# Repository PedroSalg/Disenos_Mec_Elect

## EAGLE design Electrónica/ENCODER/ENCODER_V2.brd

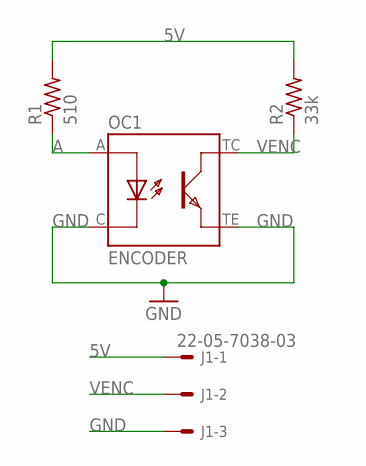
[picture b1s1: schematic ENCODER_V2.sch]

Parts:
J1: 22-05-7038-03; 7395-03
OC1: ENCODER; PI_GP1S53VJ000F
R1: 510; R0805
R2: 33k; R0805

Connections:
5V: J1.1, R1.2, R2.2
A: OC1.A, R1.1
GND: J1.3, OC1.C, OC1.TE
VENC: J1.2, OC1.TC, R2.1

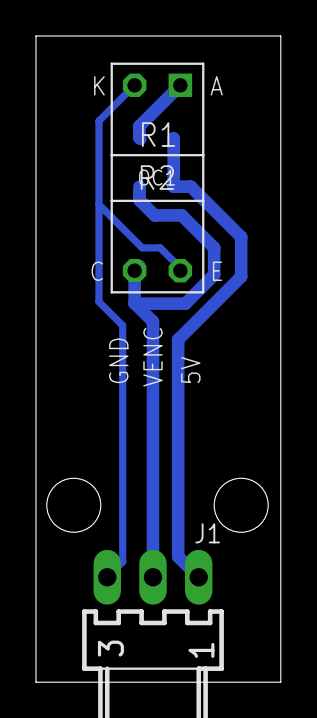
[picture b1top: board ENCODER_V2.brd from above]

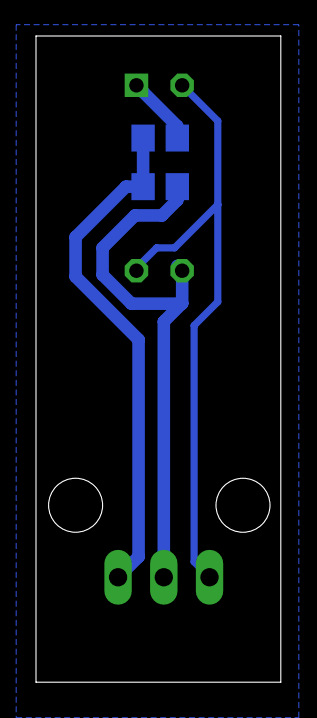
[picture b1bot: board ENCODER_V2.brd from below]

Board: 2 copper layers, 13.6 x 35.9 mm, 4 parts (2 on the bottom side), 4 nets.

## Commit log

2020-05-16 Actualizacion
2020-05-16 maquina_estados_escritura
2020-07-11 Esquemas en formato dia para el libro
2020-07-11 Diseño final integrador 3
2020-07-11 Diseño final tarjeta capa 3 ADC Memoria para la estacion
